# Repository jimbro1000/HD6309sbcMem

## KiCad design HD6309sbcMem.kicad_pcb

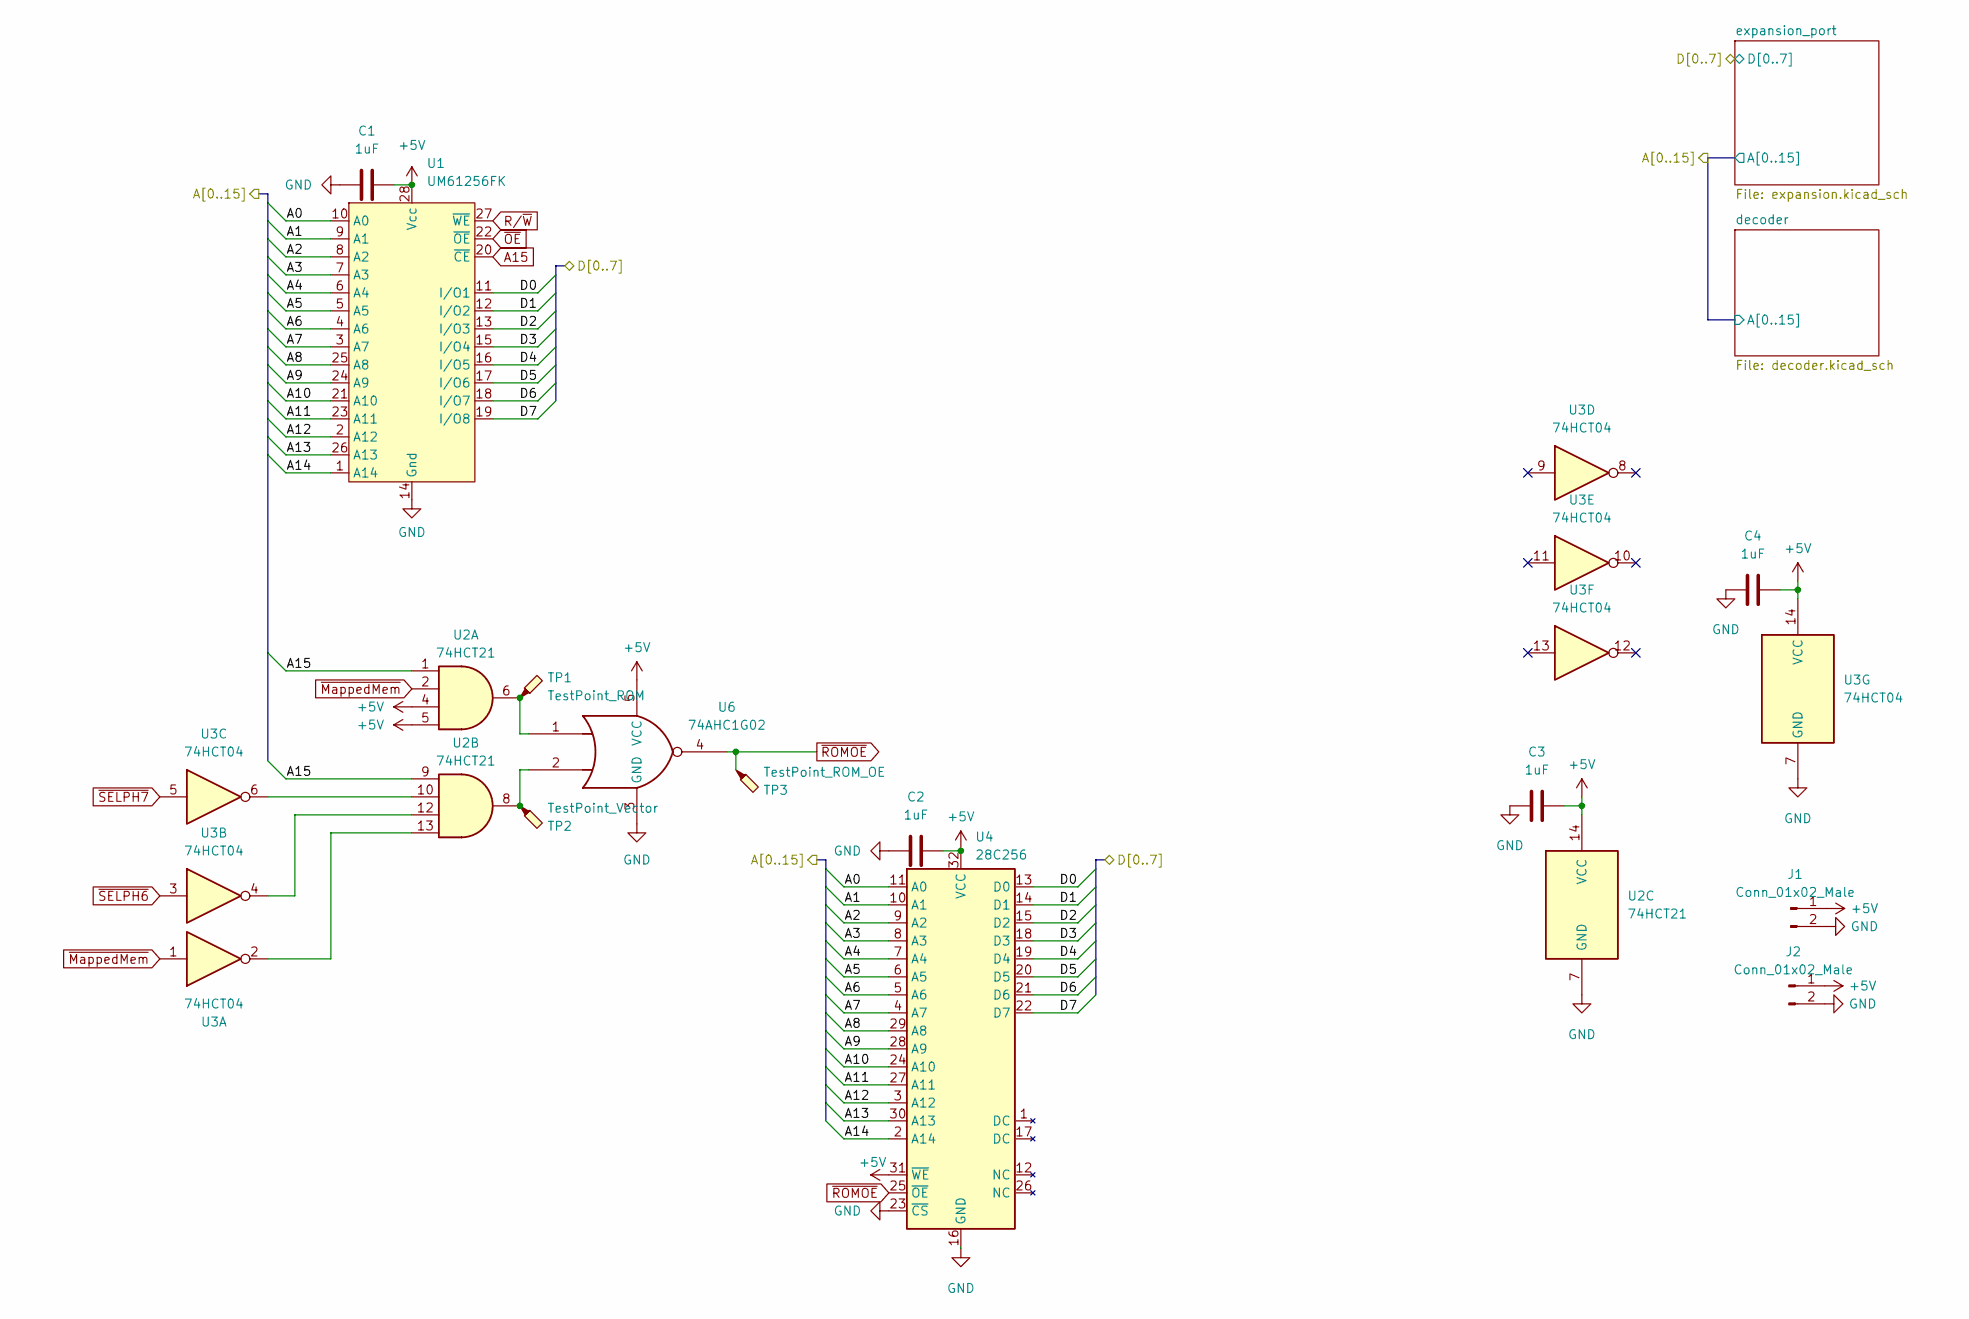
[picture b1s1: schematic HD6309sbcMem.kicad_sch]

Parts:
C1, C2, C3, C4: 1uF; C_0805_2012Metric_Pad1.18x1.45mm_HandSolder
J1, J2: Conn_01x02_Male; PinHeader_1x02_P2.54mm_Vertical
TP1: TestPoint_ROM; TestPoint_Pad_D1.5mm
TP2: TestPoint_Vector; TestPoint_Pad_D1.5mm
TP3: TestPoint_ROM_OE; TestPoint_Pad_D1.5mm
U1: UM61256FK; DIP-28_W7.62mm
U2: 74HCT21; SOIC-14_3.9x8.7mm_P1.27mm
U3: 74HCT04; SOIC-14_3.9x8.7mm_P1.27mm
U4: 28C256; PLCC-32_THT-Socket
U6: 74AHC1G02; SOT-23-5_HandSoldering

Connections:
+5V: C1.2, C2.2, C3.2, C4.2, J1.1, J2.1, U1.28 (Vcc), U2.4, U2.5, U2.14 (VCC), U3.14 (VCC), U4.31 (~WE), U4.32 (VCC), U6.5 (VCC); also elsewhere on the board
/A0: U1.10 (A0), U4.11 (A0); also elsewhere on the board
/A1: U1.9 (A1), U4.10 (A1); also elsewhere on the board
/A2: U1.8 (A2), U4.9 (A2); also elsewhere on the board
/A3: U1.7 (A3), U4.8 (A3); also elsewhere on the board
/A4: U1.6 (A4), U4.7 (A4); also elsewhere on the board
/A5: U1.5 (A5), U4.6 (A5); also elsewhere on the board
/A6: U1.4 (A6), U4.5 (A6); also elsewhere on the board
/A7: U1.3 (A7), U4.4 (A7); also elsewhere on the board
/A8: U1.25 (A8), U4.29 (A8); also elsewhere on the board
/A9: U1.24 (A9), U4.28 (A9); also elsewhere on the board
/A10: U1.21 (A10), U4.24 (A10); also elsewhere on the board
/A11: U1.23 (A11), U4.27 (A11); also elsewhere on the board
/A12: U1.2 (A12), U4.3 (A12); also elsewhere on the board
/A13: U1.26 (A13), U4.30 (A13); also elsewhere on the board
/A14: U1.1 (A14), U4.2 (A14); also elsewhere on the board
/D0: U1.11 (I/O1), U4.13 (D0); also elsewhere on the board
/D1: U1.12 (I/O2), U4.14 (D1); also elsewhere on the board
/D2: U1.13 (I/O3), U4.15 (D2); also elsewhere on the board
/D3: U1.15 (I/O4), U4.18 (D3); also elsewhere on the board
/D4: U1.16 (I/O5), U4.19 (D4); also elsewhere on the board
/D5: U1.17 (I/O6), U4.20 (D5); also elsewhere on the board
/D6: U1.18 (I/O7), U4.21 (D6); also elsewhere on the board
/D7: U1.19 (I/O8), U4.22 (D7); also elsewhere on the board
A15: U1.20 (~CE), U2.1, U2.9; also elsewhere on the board
GND: C1.1, C2.1, C3.1, C4.1, J1.2, J2.2, U1.14 (Gnd), U2.7 (GND), U3.7 (GND), U4.16 (GND), U4.23 (~CS), U6.3 (GND); also elsewhere on the board
unnamed: TP1.1, U2.6, U6.1
unnamed: TP2.1, U2.8, U6.2
unnamed: U2.10, U3.6
unnamed: U2.12, U3.4
unnamed: U2.13, U3.2
R/~W: U1.27 (~WE); also elsewhere on the board
~MappedMem: U2.2, U3.1; also elsewhere on the board
~OE: U1.22 (~OE)
~ROMOE: TP3.1, U4.25 (~OE), U6.4
~SELPH6: U3.3; also elsewhere on the board
~SELPH7: U3.5; also elsewhere on the board

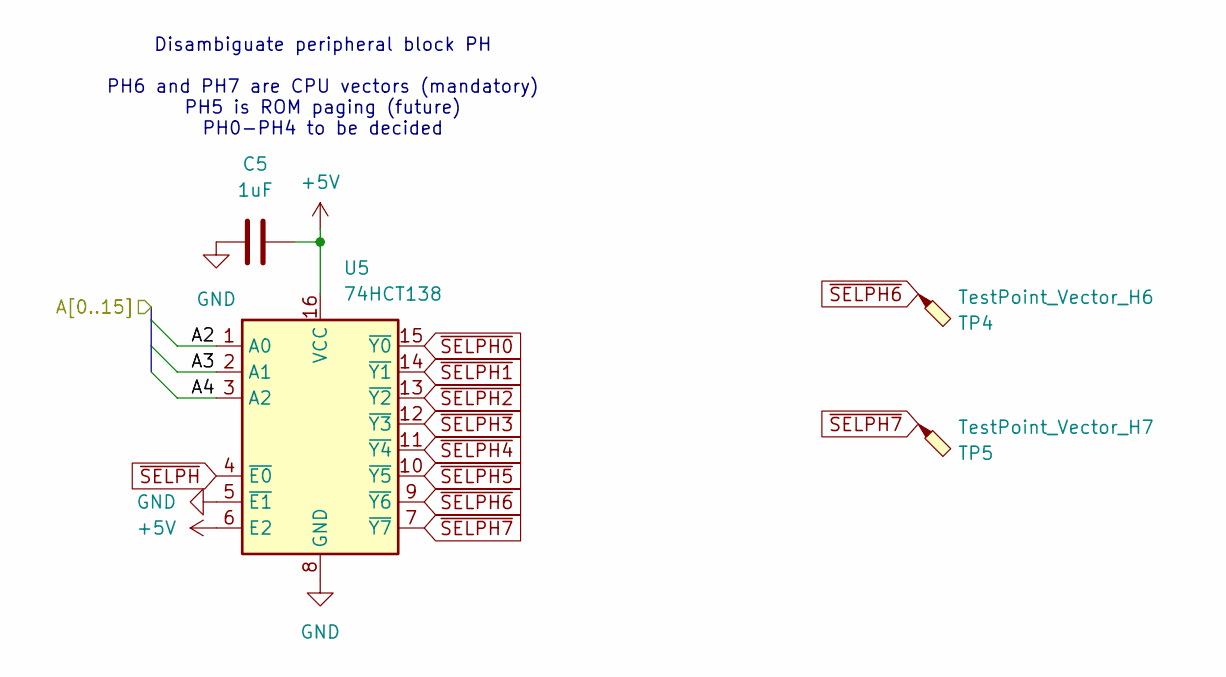
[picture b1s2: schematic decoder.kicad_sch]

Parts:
C5: 1uF; C_0805_2012Metric_Pad1.18x1.45mm_HandSolder
TP4: TestPoint_Vector_H6; TestPoint_Pad_D1.5mm
TP5: TestPoint_Vector_H7; TestPoint_Pad_D1.5mm
U5: 74HCT138; SOIC-16_3.9x9.9mm_P1.27mm

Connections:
+5V: C5.2, U5.6 (E2), U5.16 (VCC); also elsewhere on the board
/A2: U5.1 (A0); also elsewhere on the board
/A3: U5.2 (A1); also elsewhere on the board
/A4: U5.3 (A2); also elsewhere on the board
GND: C5.1, U5.5 (~E1), U5.8 (GND); also elsewhere on the board
~SELPH0: U5.15 (~Y0)
~SELPH1: U5.14 (~Y1)
~SELPH2: U5.13 (~Y2)
~SELPH3: U5.12 (~Y3)
~SELPH4: U5.11 (~Y4)
~SELPH5: U5.10 (~Y5)
~SELPH6: TP4.1, U5.9 (~Y6); also elsewhere on the board
~SELPH7: TP5.1, U5.7 (~Y7); also elsewhere on the board
~SELPH: U5.4 (~E0); also elsewhere on the board

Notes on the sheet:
Disambiguate peripheral block PH PH6 and PH7 are CPU vectors (mandatory) PH5 is ROM paging (future) PH0-PH4 to be decided

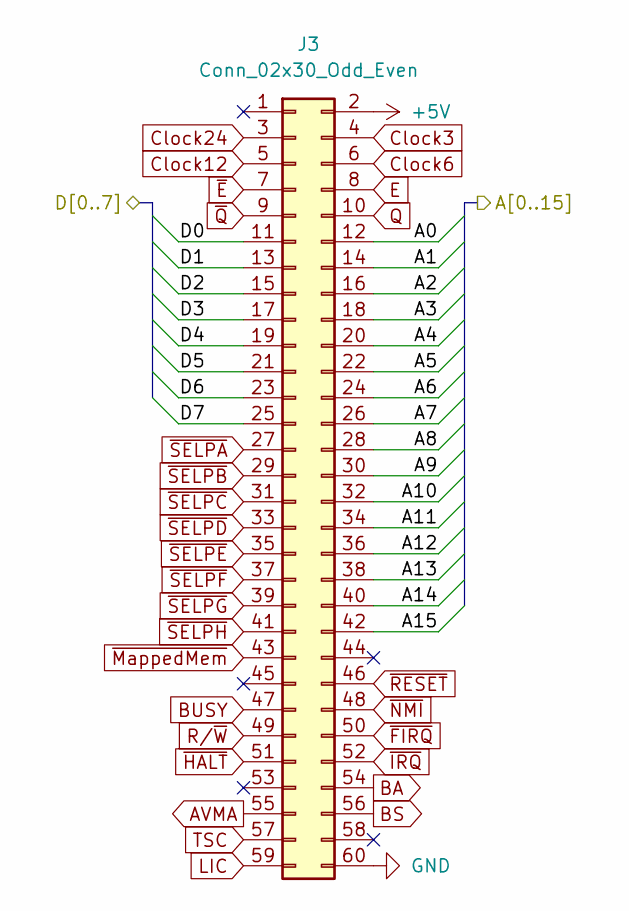
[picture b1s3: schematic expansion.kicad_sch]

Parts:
J3: Conn_02x30_Odd_Even; PinHeader_2x30_P2.54mm_Vertical

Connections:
+5V: J3.2; also elsewhere on the board
/A0: J3.12; also elsewhere on the board
/A1: J3.14; also elsewhere on the board
/A2: J3.16; also elsewhere on the board
/A3: J3.18; also elsewhere on the board
/A4: J3.20; also elsewhere on the board
/A5: J3.22; also elsewhere on the board
/A6: J3.24; also elsewhere on the board
/A7: J3.26; also elsewhere on the board
/A8: J3.28; also elsewhere on the board
/A9: J3.30; also elsewhere on the board
/A10: J3.32; also elsewhere on the board
/A11: J3.34; also elsewhere on the board
/A12: J3.36; also elsewhere on the board
/A13: J3.38; also elsewhere on the board
/A14: J3.40; also elsewhere on the board
/D0: J3.11; also elsewhere on the board
/D1: J3.13; also elsewhere on the board
/D2: J3.15; also elsewhere on the board
/D3: J3.17; also elsewhere on the board
/D4: J3.19; also elsewhere on the board
/D5: J3.21; also elsewhere on the board
/D6: J3.23; also elsewhere on the board
/D7: J3.25; also elsewhere on the board
A15: J3.42; also elsewhere on the board
AVMA: J3.55
BA: J3.54
BS: J3.56
BUSY: J3.47
Clock3: J3.4
Clock6: J3.6
Clock12: J3.5
Clock24: J3.3
E: J3.8
GND: J3.60; also elsewhere on the board
LIC: J3.59
Q: J3.10
R/~W: J3.49; also elsewhere on the board
TSC: J3.57
~E: J3.7
~FIRQ: J3.50
~HALT: J3.51
~IRQ: J3.52
~MappedMem: J3.43; also elsewhere on the board
~NMI: J3.48
~Q: J3.9
~RESET: J3.46
~SELPA: J3.27
~SELPB: J3.29
~SELPC: J3.31
~SELPD: J3.33
~SELPE: J3.35
~SELPF: J3.37
~SELPG: J3.39
~SELPH: J3.41; also elsewhere on the board

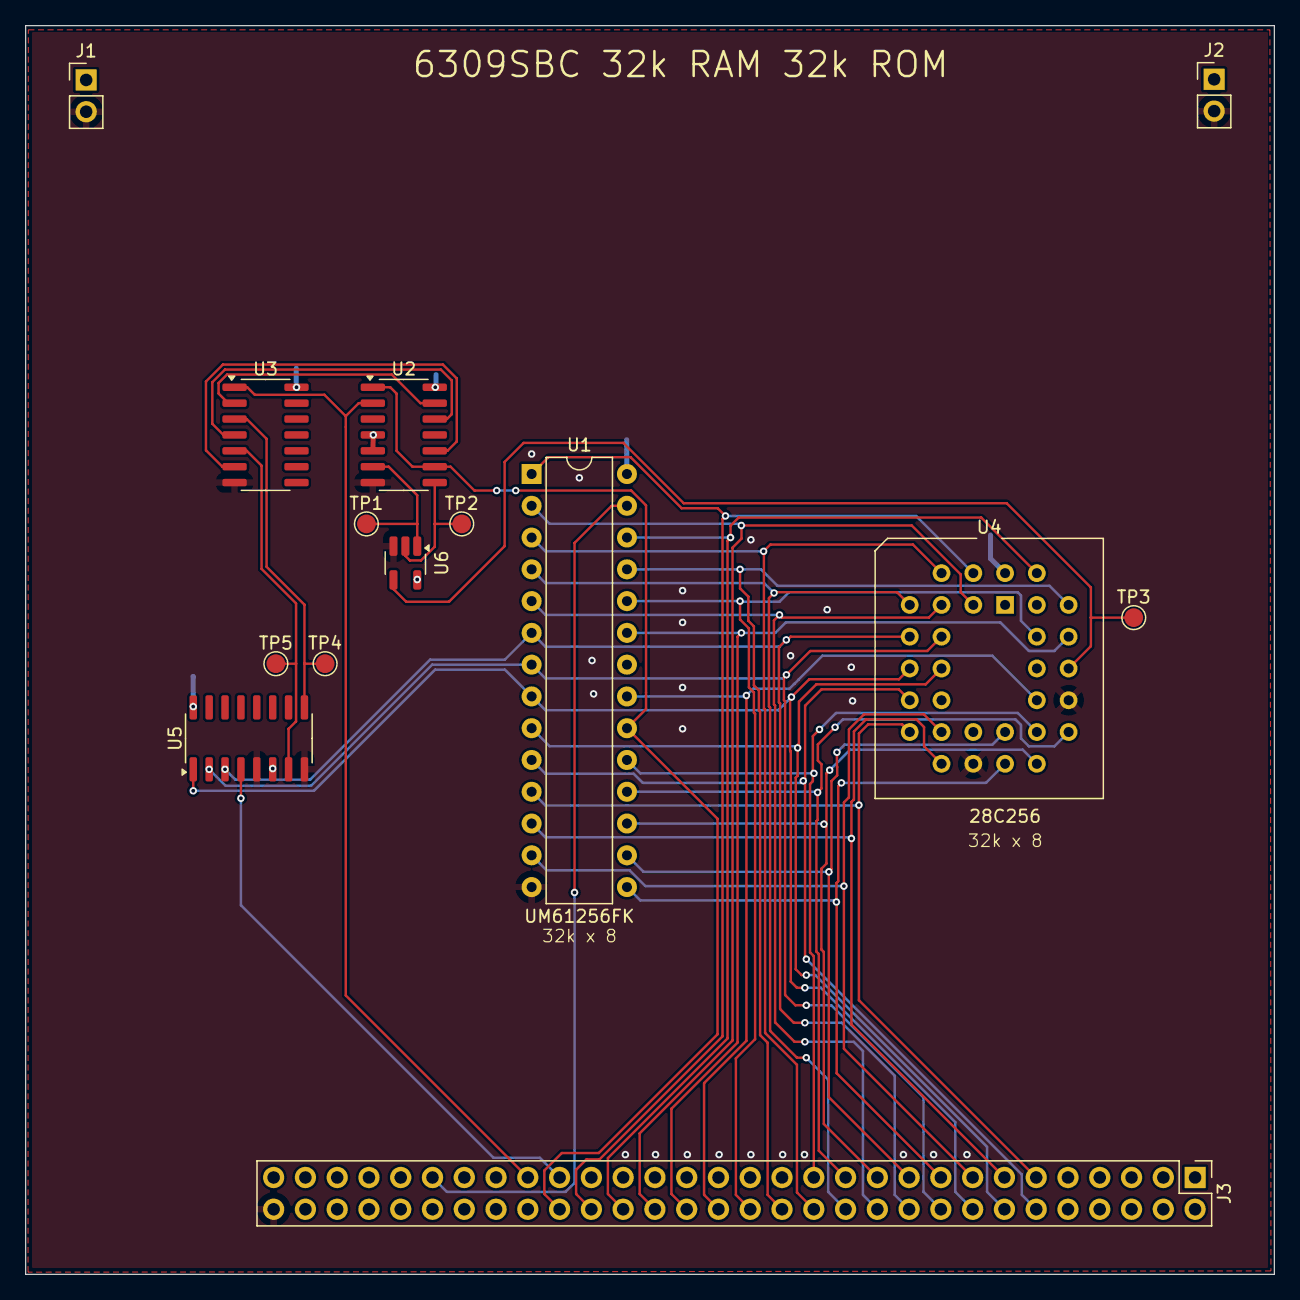
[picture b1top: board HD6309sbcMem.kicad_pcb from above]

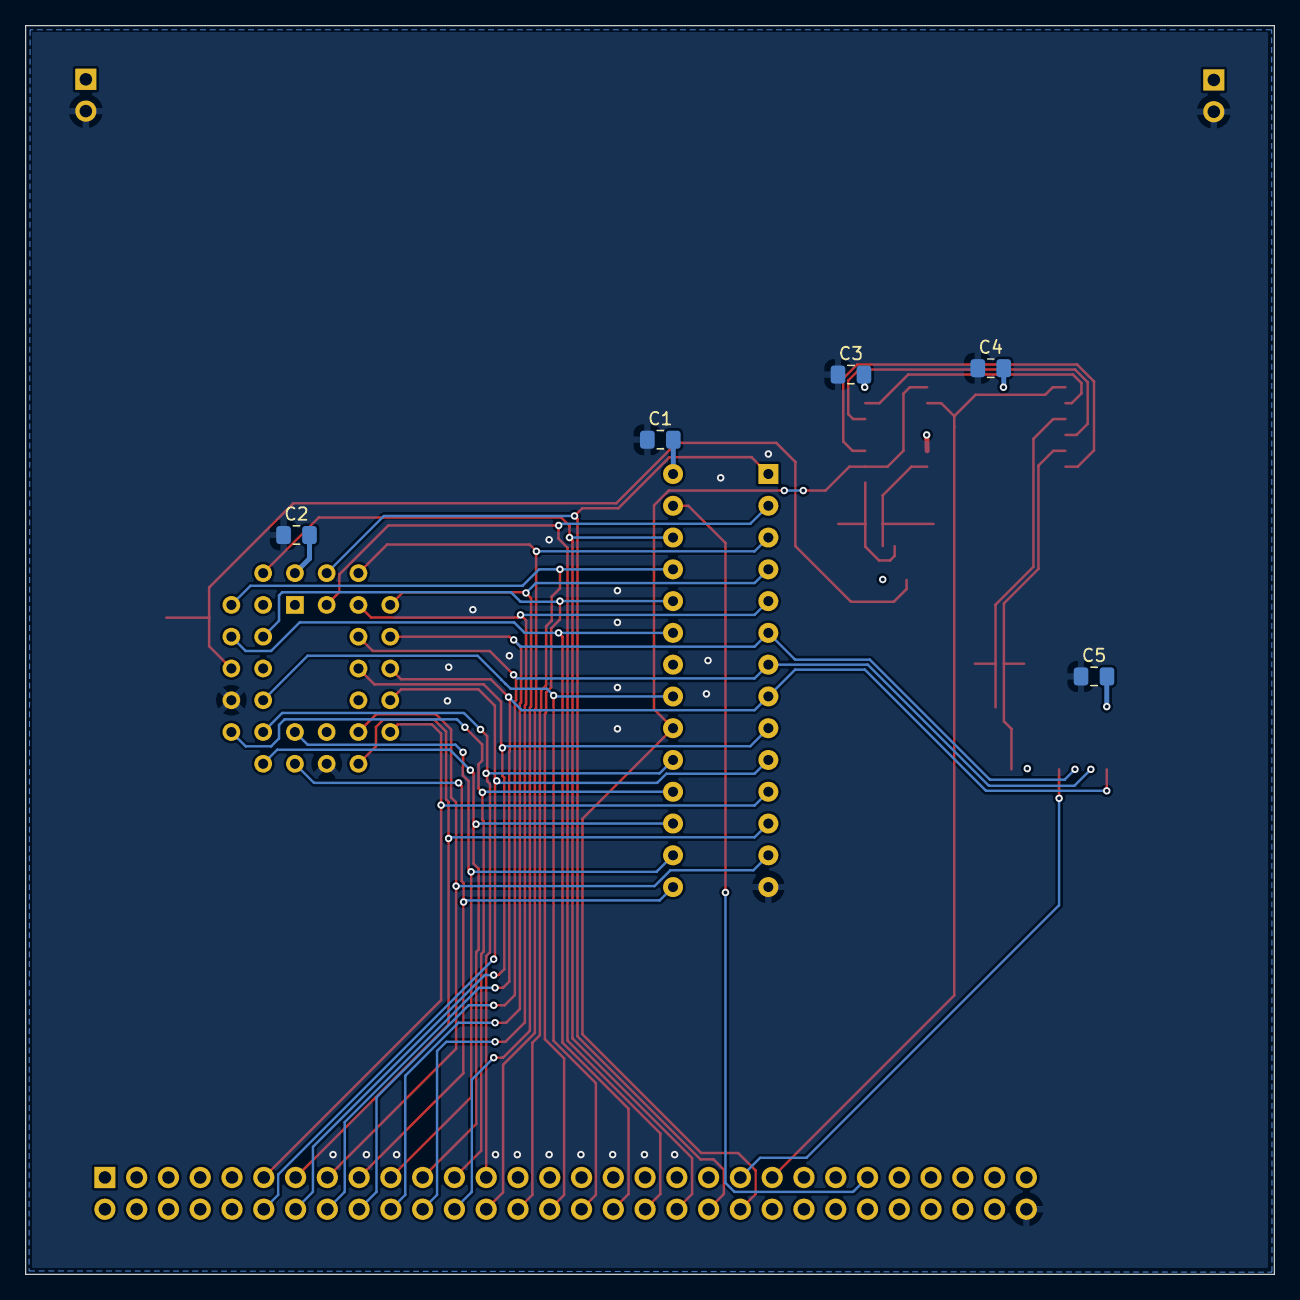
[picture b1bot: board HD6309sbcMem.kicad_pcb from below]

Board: 4 copper layers, 99.8 x 99.8 mm, 19 parts (5 on the bottom side), 37 nets.
